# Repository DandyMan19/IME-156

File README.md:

# IME-156
Stuff done and needed for IME 156.

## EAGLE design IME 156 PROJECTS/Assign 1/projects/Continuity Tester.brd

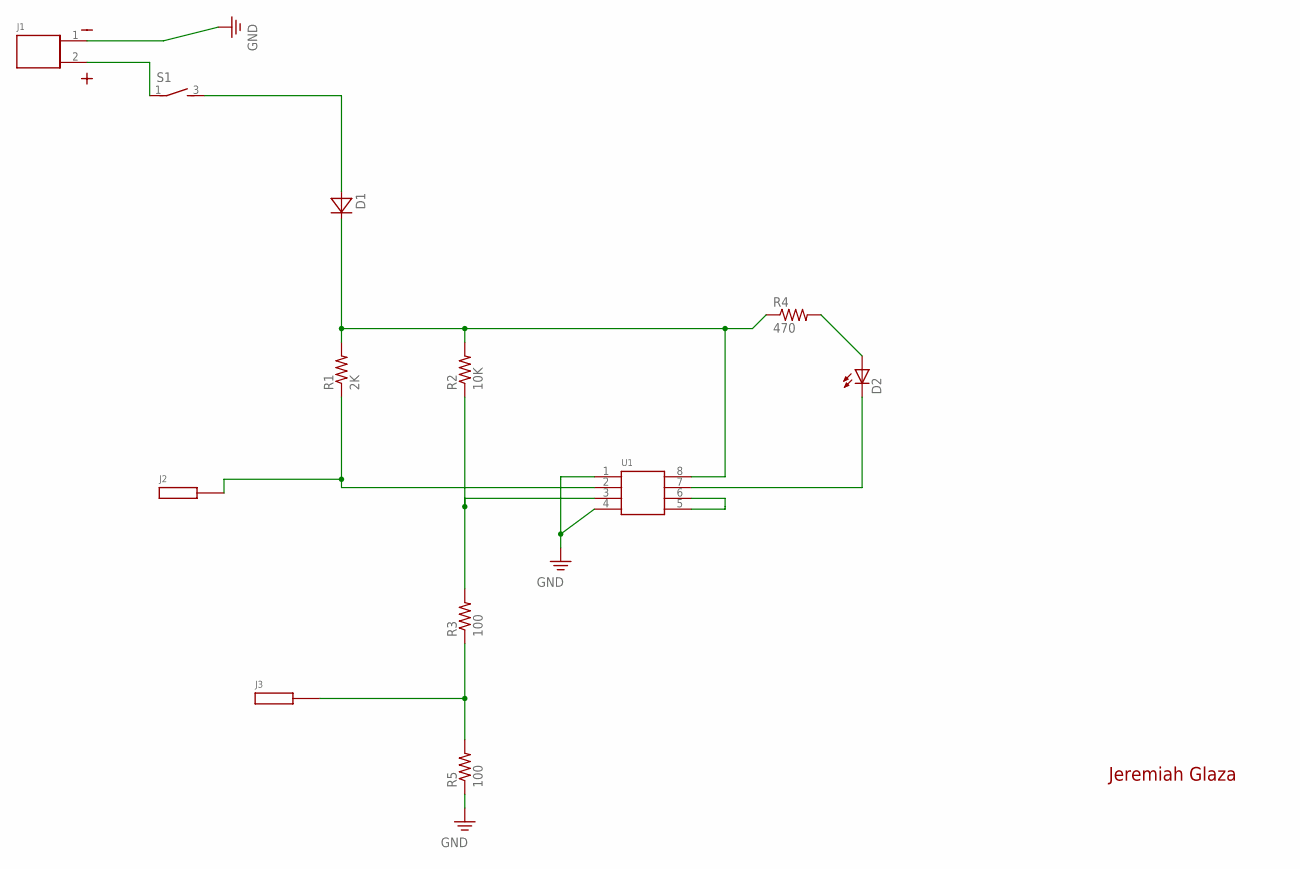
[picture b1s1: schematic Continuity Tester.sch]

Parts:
D1: DIODE; DIODE-FOOT
D2: LED; LED-FOOT
J1: POWER; POWER-FOOT
J2, J3: ALLIGATORCLIP; ALLIGATORCLIP-FOOT
R1: 2K; RES-FOOT
R2: 10K; RES-FOOT
R3, R5: 100; RES-FOOT
R4: 470; RES-FOOT
S1: SWITCH; SWITCH-FOOT
U1: LM311M; LM311M-FOOT

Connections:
unnamed: J1.2, S1.1
unnamed: D1.A, S1.3
unnamed: U1.5, U1.6
unnamed: D1.C, R1.2, R2.2, R4.1, U1.8
unnamed: D2.A, R4.2
unnamed: D2.C, U1.7
unnamed: J2.1, R1.1, U1.2
unnamed: R2.1, R3.2, U1.3
unnamed: J3.1, R3.1, R5.2
PE: J1.1, R5.1, U1.1, U1.4

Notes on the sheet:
Jeremiah Glaza

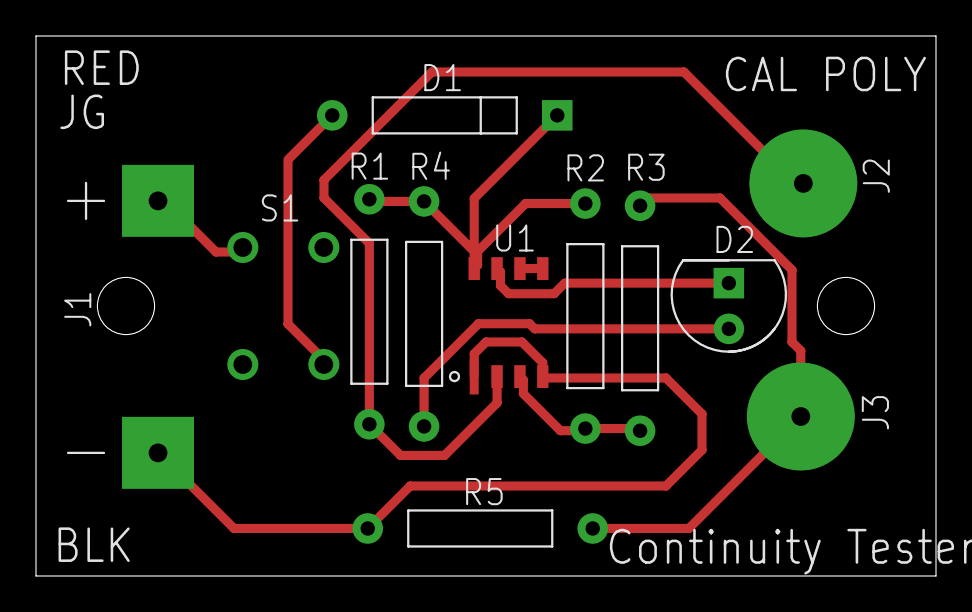
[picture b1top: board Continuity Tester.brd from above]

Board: 2 copper layers, 50.0 x 30.0 mm, 12 parts (0 on the bottom side), 10 nets.

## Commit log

2019-06-26 Add files via upload
    Stuff needed for the lab.
